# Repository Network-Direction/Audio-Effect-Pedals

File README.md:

# Effects Pedal Resources
Schematics and other resources for building effects pedals.

Schematics are drawn in Kicad.

Sometimes fabrication files are included, for use with services such as JLCPCB.

Enclosure templates show how to drill an enclosure.

</br></br>

# Pedals
Distortion:
* Big Muff Pi
* Boss BD2 Blues Driver (original and modified)
* OpAmp Distortion pedal
* Klon Centaur
* MXR Distortion
* ProCo RAT

</br></br>

Other:
* Boss CE-2 Chorus
* Boss PH-1r Phaser
* MXR Dyna Comp

</br></br>

# Audio Theory
Learn the basics of how sound works, at least as far as it relates to effects pedals.

See the Wiki page for more.

</br></br>

# Audio Circuit Blocks
Learn how some of the circuit blocks common in effects pedals work.

# KiCad Components
Additional libraries for KiCad, for components that don't exist by default.

</br></br>

# Stomp Breakout
A small breakout board for the stomp switch, and parts that connect to it.

</br></br>

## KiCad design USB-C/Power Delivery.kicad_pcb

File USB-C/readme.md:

# USB-C Power

A USB power system supplying 4x 9v outputs, up tp 2A or current.

Requires a USB-C charger capable of 9v/2A or better. A red LED turns on of there's an error negotiating power.

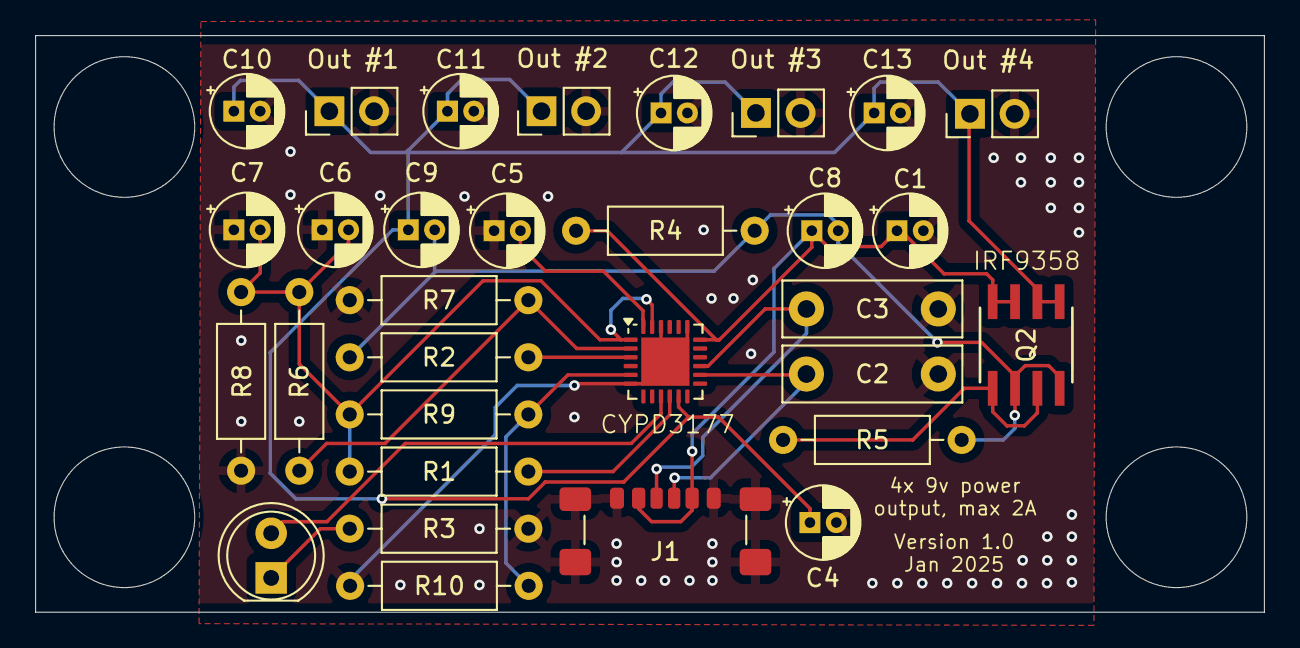
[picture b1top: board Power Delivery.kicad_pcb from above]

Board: 2 copper layers, 69.9 x 32.8 mm, 31 parts (0 on the bottom side), 15 nets.

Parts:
C1: 3.3uF; CP_Radial_D4.0mm_P1.50mm
C2, C3: 470pf; C_Rect_L10.0mm_W3.0mm_P7.50mm_MKS4
C4, C5, C6, C8, C9: 1uF; CP_Radial_D4.0mm_P1.50mm
C7: 0.1uF; CP_Radial_D4.0mm_P1.50mm
C10, C11, C12, C13: 100uF; CP_Radial_D4.0mm_P1.50mm
D1: LED; LED_D5.0mm
J1: USB4125-GF-A; USB_C_Receptacle_GCT_USB4135-GF-A_6P_TopMnt_Horizontal
J2: Out #3; PinHeader_1x02_P2.54mm_Vertical
J3: Out #1; PinHeader_1x02_P2.54mm_Vertical
J4: Out #2; PinHeader_1x02_P2.54mm_Vertical
J5: Out #4; PinHeader_1x02_P2.54mm_Vertical
Q2: IRF9358-TRPBF
R1: 4K7; R_Axial_DIN0207_L6.3mm_D2.5mm_P10.16mm_Horizontal
R2, R7: 1K; R_Axial_DIN0207_L6.3mm_D2.5mm_P10.16mm_Horizontal
R3, R10: 2K4; R_Axial_DIN0207_L6.3mm_D2.5mm_P10.16mm_Horizontal
R4: 10K; R_Axial_DIN0207_L6.3mm_D2.5mm_P10.16mm_Horizontal
R5: 47K; R_Axial_DIN0207_L6.3mm_D2.5mm_P10.16mm_Horizontal
R6, R8, R9: 5K1; R_Axial_DIN0207_L6.3mm_D2.5mm_P10.16mm_Horizontal
U1: CYPD3177-24LQ; QFN-24-1EP_4x4mm_P0.5mm_EP2.75x2.75mm

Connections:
3.3v: C6.2, C7.2, R1.2, R6.1, R8.1, R9.1, U1.1 (VBUS_MIN), U1.23 (VDDD)
GND: C1.2, C2.2, C3.2, C4.2, C5.1, C6.1, C7.1, C10.2, C11.2, C12.2, C13.2, J1.A12 (GND), J1.B12 (GND), J1.S1 (SHIELD), J2.2, J3.2, J4.2, J5.2, R3.1, R7.1, R8.2, R10.1, U1.6 (ISNK_FINE), U1.19 (GND), U1.22 (GND), U1.25 (GND)
unnamed: C8.2, C9.2, Q2.2, Q2.4, R2.1, R4.2, R5.2
unnamed: D1.2 (A), U1.9 (FAULT)
unnamed: D1.1 (K), R3.2
unnamed: C3.1, J1.A5 (CC1), U1.15 (CC1)
unnamed: C2.1, J1.B5 (CC2), U1.14 (CC2)
unnamed: C4.1, C9.1, C10.1, C11.1, C12.1, C13.1, J2.1, J3.1, J4.1, J5.1, Q2.5, Q2.6, U1.11 (VDC_OUT)
unnamed: Q2.1, Q2.3, R5.1
unnamed: R1.1, U1.10 (FLIP)
unnamed: R9.2, R10.2, U1.5 (ISNK_COARSE)
unnamed: R2.2, U1.3 (VBUS_FET_EN)
unnamed: C1.1, C8.1, J1.A9 (VBUS), J1.B9 (VBUS), Q2.7, Q2.8, R4.1, U1.18 (VBUS_IN)
unnamed: R6.2, R7.2, U1.2 (VBUS_MAX)
unnamed: C5.2, U1.24 (VCCD)

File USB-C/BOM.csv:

"Reference","Value","Datasheet","Footprint","Qty","DNP"
"C1","3.3uF","~","Capacitor_THT:CP_Radial_D4.0mm_P1.50mm","1",""
"C2,C3","470pf","~","Capacitor_THT:C_Rect_L10.0mm_W3.0mm_P7.50mm_MKS4","2",""
"C4,C5,C6,C8,C9","1uF","~","Capacitor_THT:CP_Radial_D4.0mm_P1.50mm","5",""
"C7","0.1uF","~","Capacitor_THT:CP_Radial_D4.0mm_P1.50mm","1",""
"C10,C11,C12,C13","100uF","~","Capacitor_THT:CP_Radial_D4.0mm_P1.50mm","4",""
"D1","LED","~","LED_THT:LED_D5.0mm","1",""
"J1","USB4125-GF-A","https://www.usb.org/sites/default/files/documents/usb_type-c.zip","Connector_USB:USB_C_Receptacle_GCT_USB4135-GF-A_6P_TopMnt_Horizontal","1",""
"J2","Out #3","~","Connector_PinHeader_2.54mm:PinHeader_1x02_P2.54mm_Vertical","1",""
"J3","Out #1","~","Connector_PinHeader_2.54mm:PinHeader_1x02_P2.54mm_Vertical","1",""
"J4","Out #2","~","Connector_PinHeader_2.54mm:PinHeader_1x02_P2.54mm_Vertical","1",""
"J5","Out #4","~","Connector_PinHeader_2.54mm:PinHeader_1x02_P2.54mm_Vertical","1",""
"Q2","IRF9358-TRPBF","IRF9358TRPBF","custom:IRF9358-TRPBF","1",""
"R1","4K7","~","Resistor_THT:R_Axial_DIN0207_L6.3mm_D2.5mm_P10.16mm_Horizontal","1",""
"R2,R7","1K","~","Resistor_THT:R_Axial_DIN0207_L6.3mm_D2.5mm_P10.16mm_Horizontal","2",""
"R3,R10","2K4","~","Resistor_THT:R_Axial_DIN0207_L6.3mm_D2.5mm_P10.16mm_Horizontal","2",""
"R4","10K","~","Resistor_THT:R_Axial_DIN0207_L6.3mm_D2.5mm_P10.16mm_Horizontal","1",""
"R5","47K","~","Resistor_THT:R_Axial_DIN0207_L6.3mm_D2.5mm_P10.16mm_Horizontal","1",""
"R6,R8,R9","5K1","~","Resistor_THT:R_Axial_DIN0207_L6.3mm_D2.5mm_P10.16mm_Horizontal","3",""
"U1","CYPD3177-24LQ","https://www.infineon.com/dgdl/Infineon-EZ-PD_BCR_Datasheet_U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","Package_DFN_QFN:QFN-24-1EP_4x4mm_P0.5mm_EP2.75x2.75mm","1",""

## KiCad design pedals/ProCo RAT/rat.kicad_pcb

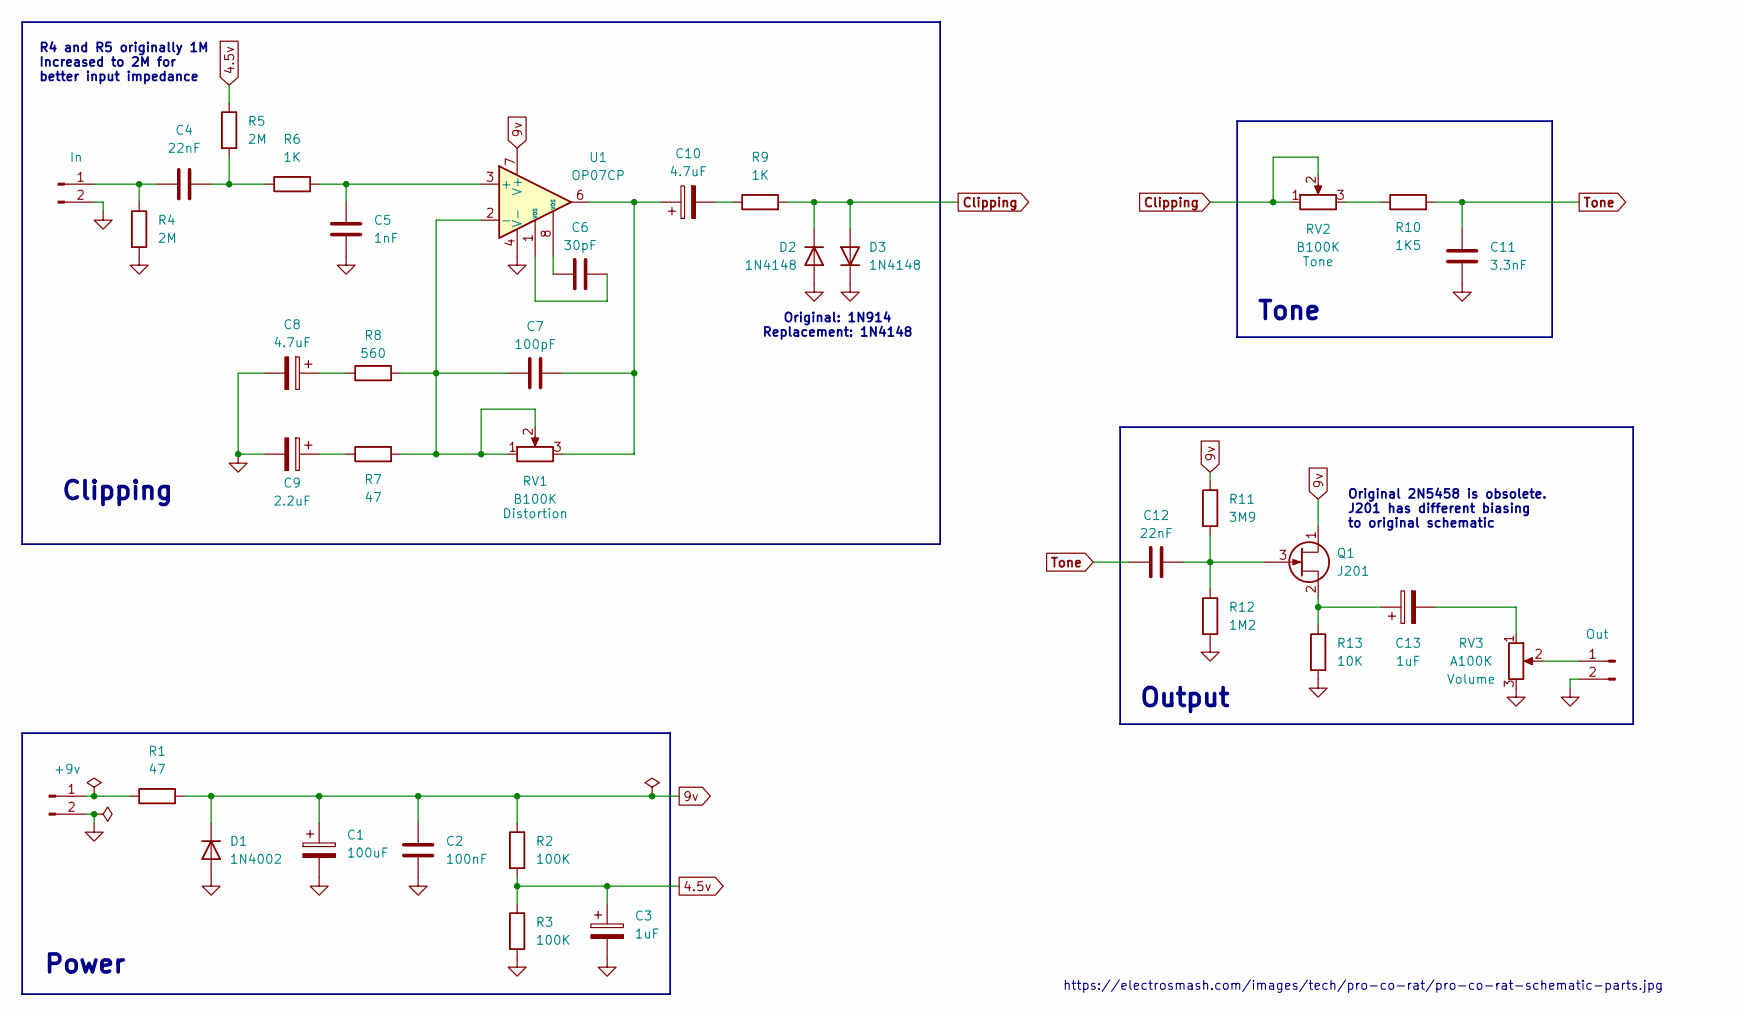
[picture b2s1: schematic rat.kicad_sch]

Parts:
C1: 100uF; CP_Radial_D6.3mm_P2.50mm
C2: 100nF; C_Rect_L7.2mm_W2.5mm_P5.00mm_FKS2_FKP2_MKS2_MKP2
C3, C13: 1uF; CP_Radial_D4.0mm_P1.50mm
C4, C12: 22nF; C_Rect_L7.2mm_W2.5mm_P5.00mm_FKS2_FKP2_MKS2_MKP2
C5: 1nF; C_Rect_L7.2mm_W2.5mm_P5.00mm_FKS2_FKP2_MKS2_MKP2
C6: 30pF; C_Disc_D3.8mm_W2.6mm_P2.50mm
C7: 100pF; C_Disc_D5.1mm_W3.2mm_P5.00mm
C8, C10: 4.7uF; CP_Radial_D4.0mm_P1.50mm
C9: 2.2uF; C_Rect_L7.2mm_W2.5mm_P5.00mm_FKS2_FKP2_MKS2_MKP2
C11: 3.3nF; C_Rect_L7.2mm_W2.5mm_P5.00mm_FKS2_FKP2_MKS2_MKP2
D1: 1N4002; D_DO-34_SOD68_P7.62mm_Horizontal
D2, D3: 1N4148; D_DO-34_SOD68_P7.62mm_Horizontal
J1: +9v; PinHeader_1x02_P2.54mm_Vertical
J2: In; PinHeader_1x02_P2.54mm_Vertical
J3: Out; PinHeader_1x02_P2.54mm_Vertical
Q1: J201; SOT-23_Handsoldering
R1, R7: 47; R_Axial_DIN0207_L6.3mm_D2.5mm_P10.16mm_Horizontal
R2, R3: 100K; R_Axial_DIN0207_L6.3mm_D2.5mm_P10.16mm_Horizontal
R4, R5: 2M; R_Axial_DIN0207_L6.3mm_D2.5mm_P10.16mm_Horizontal
R6, R9: 1K; R_Axial_DIN0207_L6.3mm_D2.5mm_P10.16mm_Horizontal
R8: 560; R_Axial_DIN0207_L6.3mm_D2.5mm_P10.16mm_Horizontal
R10: 1K5; R_Axial_DIN0207_L6.3mm_D2.5mm_P10.16mm_Horizontal
R11: 3M9; R_Axial_DIN0207_L6.3mm_D2.5mm_P10.16mm_Horizontal
R12: 1M2; R_Axial_DIN0207_L6.3mm_D2.5mm_P10.16mm_Horizontal
R13: 10K; R_Axial_DIN0207_L6.3mm_D2.5mm_P10.16mm_Horizontal
RV1, RV2: B100K; PinHeader_1x03_P2.54mm_Vertical
RV3: A100K; PinHeader_1x03_P2.54mm_Vertical
U1: OP07CP; DIP-8_W7.62mm

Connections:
4.5v: C3.1, R2.2, R3.1, R5.1
9v: C1.1, C2.1, D1.1 (K), Q1.1 (D), R1.2, R2.1, R11.1, U1.7 (V+)
Clipping: D2.1 (K), D3.2 (A), R9.2, RV2.1, RV2.2
GND: C1.2, C2.2, C3.2, C5.2, C8.2, C9.2, C11.2, D1.2 (A), D2.2 (A), D3.1 (K), J1.2, J2.2, J3.2, R3.2, R4.2, R12.2, R13.2, RV3.3, U1.4 (V-)
unnamed: C4.2, R5.2, R6.1
unnamed: C6.1, U1.1 (VOS)
unnamed: C6.2, U1.8 (VOS)
unnamed: C8.1, R8.1
unnamed: C9.1, R7.1
unnamed: C7.1, C10.1, RV1.3, U1.6
unnamed: C10.2, R9.1
unnamed: C13.2, RV3.1
unnamed: J1.1, R1.1
unnamed: C4.1, J2.1, R4.1
unnamed: J3.1, RV3.2
unnamed: C12.1, Q1.3 (G), R11.2, R12.1
unnamed: C13.1, Q1.2 (S), R13.1
unnamed: R10.1, RV2.3
unnamed: C5.1, R6.2, U1.3 (+)
unnamed: C7.2, R7.2, R8.2, RV1.1, RV1.2, U1.2 (-)
Tone: C11.1, C12.2, R10.2

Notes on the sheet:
Output
Power
https://electrosmash.com/images/tech/pro-co-rat/pro-co-rat-schematic-parts.jpg
Clipping
Tone
R4 and R5 originally 1M Increased to 2M for better input impedance
Original: 1N914 Replacement: 1N4148
Original 2N5458 is obsolete. J201 has different biasing to original schematic

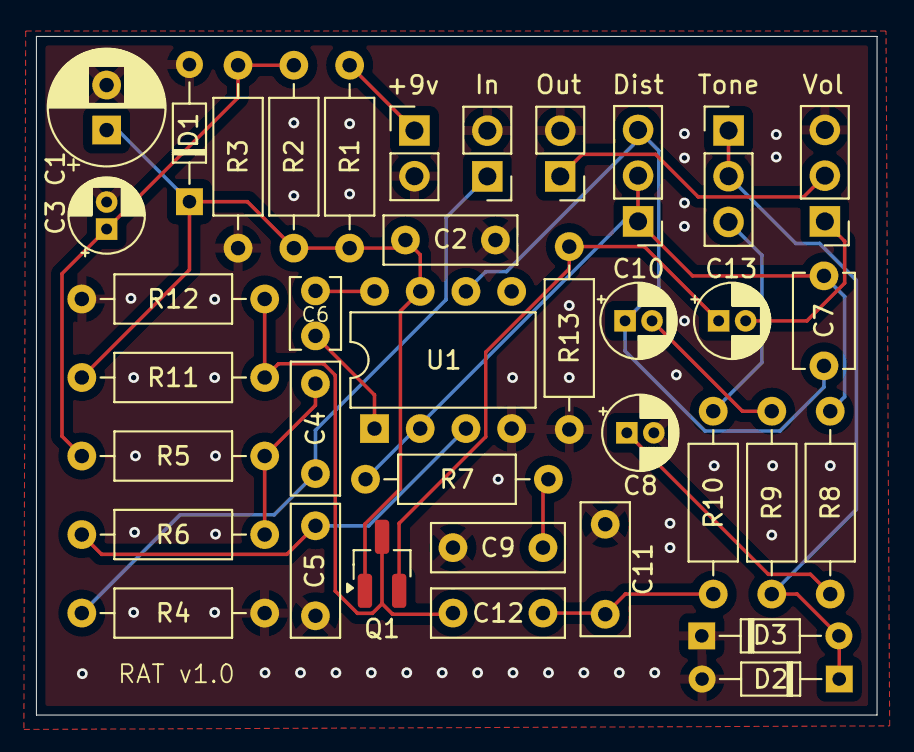
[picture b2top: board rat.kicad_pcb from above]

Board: 2 copper layers, 46.7 x 37.7 mm, 37 parts (0 on the bottom side), 21 nets.

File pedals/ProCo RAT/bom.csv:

"Id";"Designator";"Footprint";"Quantity";"Designation";"Supplier and ref";
1;"RV2,RV1";"PinHeader_1x03_P2.54mm_Vertical";2;"B100K";;;
2;"C8,C10";"CP_Radial_D4.0mm_P1.50mm";2;"4.7uF";;;
3;"Q1";"SOT-23_Handsoldering";1;"J201";;;
4;"U1";"DIP-8_W7.62mm";1;"OP07CP";;;
5;"C3,C13";"CP_Radial_D4.0mm_P1.50mm";2;"1uF";;;
6;"R12";"R_Axial_DIN0207_L6.3mm_D2.5mm_P10.16mm_Horizontal";1;"1M2";;;
7;"R6,R9";"R_Axial_DIN0207_L6.3mm_D2.5mm_P10.16mm_Horizontal";2;"1K";;;
8;"J1";"PinHeader_1x02_P2.54mm_Vertical";1;"+9v";;;
9;"D1";"D_DO-34_SOD68_P7.62mm_Horizontal";1;"1N4002";;;
10;"C12,C4";"C_Rect_L7.2mm_W2.5mm_P5.00mm_FKS2_FKP2_MKS2_MKP2";2;"22nF";;;
11;"C9";"C_Rect_L7.2mm_W2.5mm_P5.00mm_FKS2_FKP2_MKS2_MKP2";1;"2.2uF";;;
12;"J2";"PinHeader_1x02_P2.54mm_Vertical";1;"In";;;
13;"C7";"C_Disc_D5.1mm_W3.2mm_P5.00mm";1;"100pF";;;
14;"C2";"C_Rect_L7.2mm_W2.5mm_P5.00mm_FKS2_FKP2_MKS2_MKP2";1;"100nF";;;
15;"R13";"R_Axial_DIN0207_L6.3mm_D2.5mm_P10.16mm_Horizontal";1;"10K";;;
16;"R4,R5";"R_Axial_DIN0207_L6.3mm_D2.5mm_P10.16mm_Horizontal";2;"2M";;;
17;"R2,R3";"R_Axial_DIN0207_L6.3mm_D2.5mm_P10.16mm_Horizontal";2;"100K";;;
18;"C1";"CP_Radial_D6.3mm_P2.50mm";1;"100uF";;;
19;"R8";"R_Axial_DIN0207_L6.3mm_D2.5mm_P10.16mm_Horizontal";1;"560";;;
20;"C5";"C_Rect_L7.2mm_W2.5mm_P5.00mm_FKS2_FKP2_MKS2_MKP2";1;"1nF";;;
21;"RV3";"PinHeader_1x03_P2.54mm_Vertical";1;"A100K";;;
22;"C6";"C_Disc_D3.8mm_W2.6mm_P2.50mm";1;"30pF";;;
23;"D3,D2";"D_DO-34_SOD68_P7.62mm_Horizontal";2;"1N4148";;;
24;"J3";"PinHeader_1x02_P2.54mm_Vertical";1;"Out";;;
25;"R7,R1";"R_Axial_DIN0207_L6.3mm_D2.5mm_P10.16mm_Horizontal";2;"47";;;
26;"R10";"R_Axial_DIN0207_L6.3mm_D2.5mm_P10.16mm_Horizontal";1;"1K5";;;
27;"R11";"R_Axial_DIN0207_L6.3mm_D2.5mm_P10.16mm_Horizontal";1;"3M9";;;
28;"C11";"C_Rect_L7.2mm_W2.5mm_P5.00mm_FKS2_FKP2_MKS2_MKP2";1;"3.3nF";;;

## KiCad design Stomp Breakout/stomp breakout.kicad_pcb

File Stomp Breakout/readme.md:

# Stomp Breakout PCB

A PCB that allows a stomp switch to be soldered, automatically handling wiring.

Input and output jacks, as well as power are connected to the breakout.

Includes an option for a resistor and LED to show when the pedal is in bypass mode.

## Status

Schematic and PCB designed, but not yet tested.

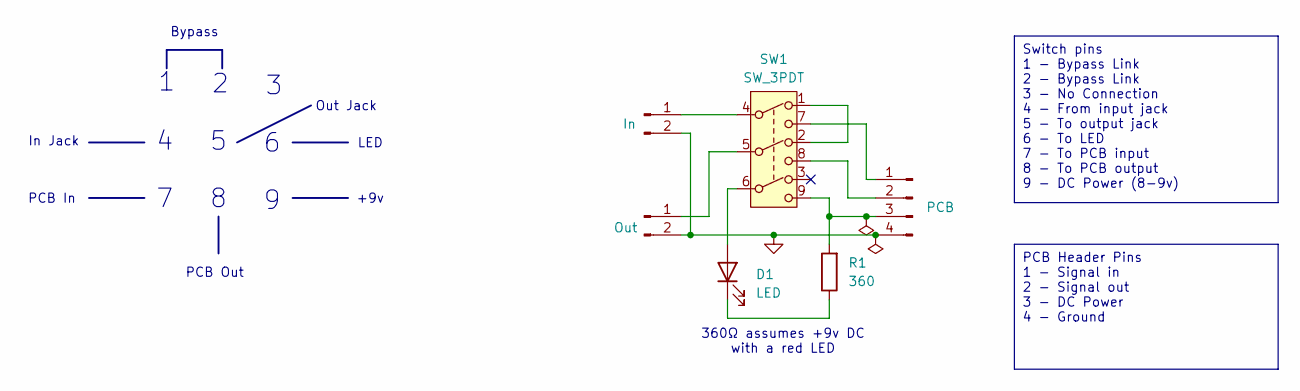
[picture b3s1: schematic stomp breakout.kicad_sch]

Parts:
D1: LED; LED_D5.0mm
J1: In; PinHeader_1x02_P2.54mm_Horizontal
J2: Out; PinHeader_1x02_P2.54mm_Horizontal
J3: PCB; PinHeader_1x04_P2.54mm_Horizontal
R1: 360; R_Axial_DIN0207_L6.3mm_D2.5mm_P7.62mm_Horizontal
SW1: SW_3PDT; 3PDT Stomp Switch

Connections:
GND: J1.2, J2.2, J3.4
unnamed: D1.2 (A), SW1.6
unnamed: D1.1 (K), R1.1
unnamed: J1.1, SW1.4
unnamed: J2.1, SW1.5
unnamed: J3.1, SW1.7
unnamed: J3.2, SW1.8
unnamed: J3.3, R1.2, SW1.9
unnamed: SW1.1, SW1.2

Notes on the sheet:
PCB Header Pins 1 - Signal in 2 - Signal out 3 - DC Power 4 - Ground
Switch pins 1 - Bypass Link 2 - Bypass Link 3 - No Connection 4 - From input jack 5 - To output jack 6 - To LED 7 - To PCB input 8 - To PCB output 9 - DC Power (8-9v)
Out Jack
In Jack
Bypass
PCB Out
360Ω assumes +9v DC with a red LED
LED
PCB In
+9v

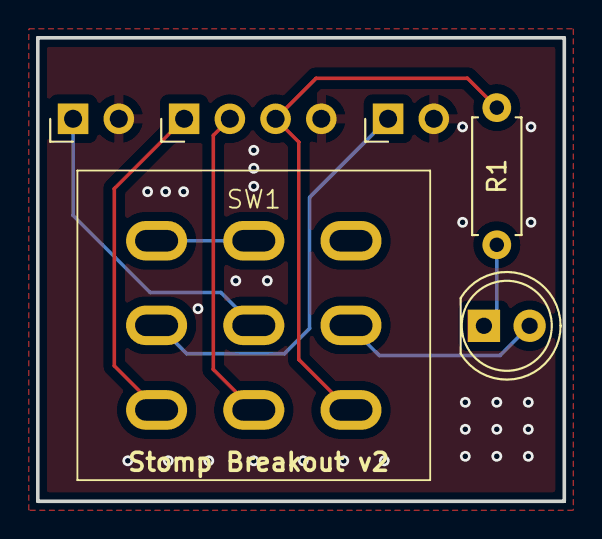
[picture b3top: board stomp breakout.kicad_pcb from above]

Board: 2 copper layers, 29.2 x 25.8 mm, 6 parts (0 on the bottom side), 9 nets.

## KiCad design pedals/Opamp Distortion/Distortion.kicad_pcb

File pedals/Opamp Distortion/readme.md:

# OpAmp Distortion

# Status
Tested on the PCB
PCB printed but not yet tested.

# Notes
A custom distortion pedal based on OpAmp rail clipping

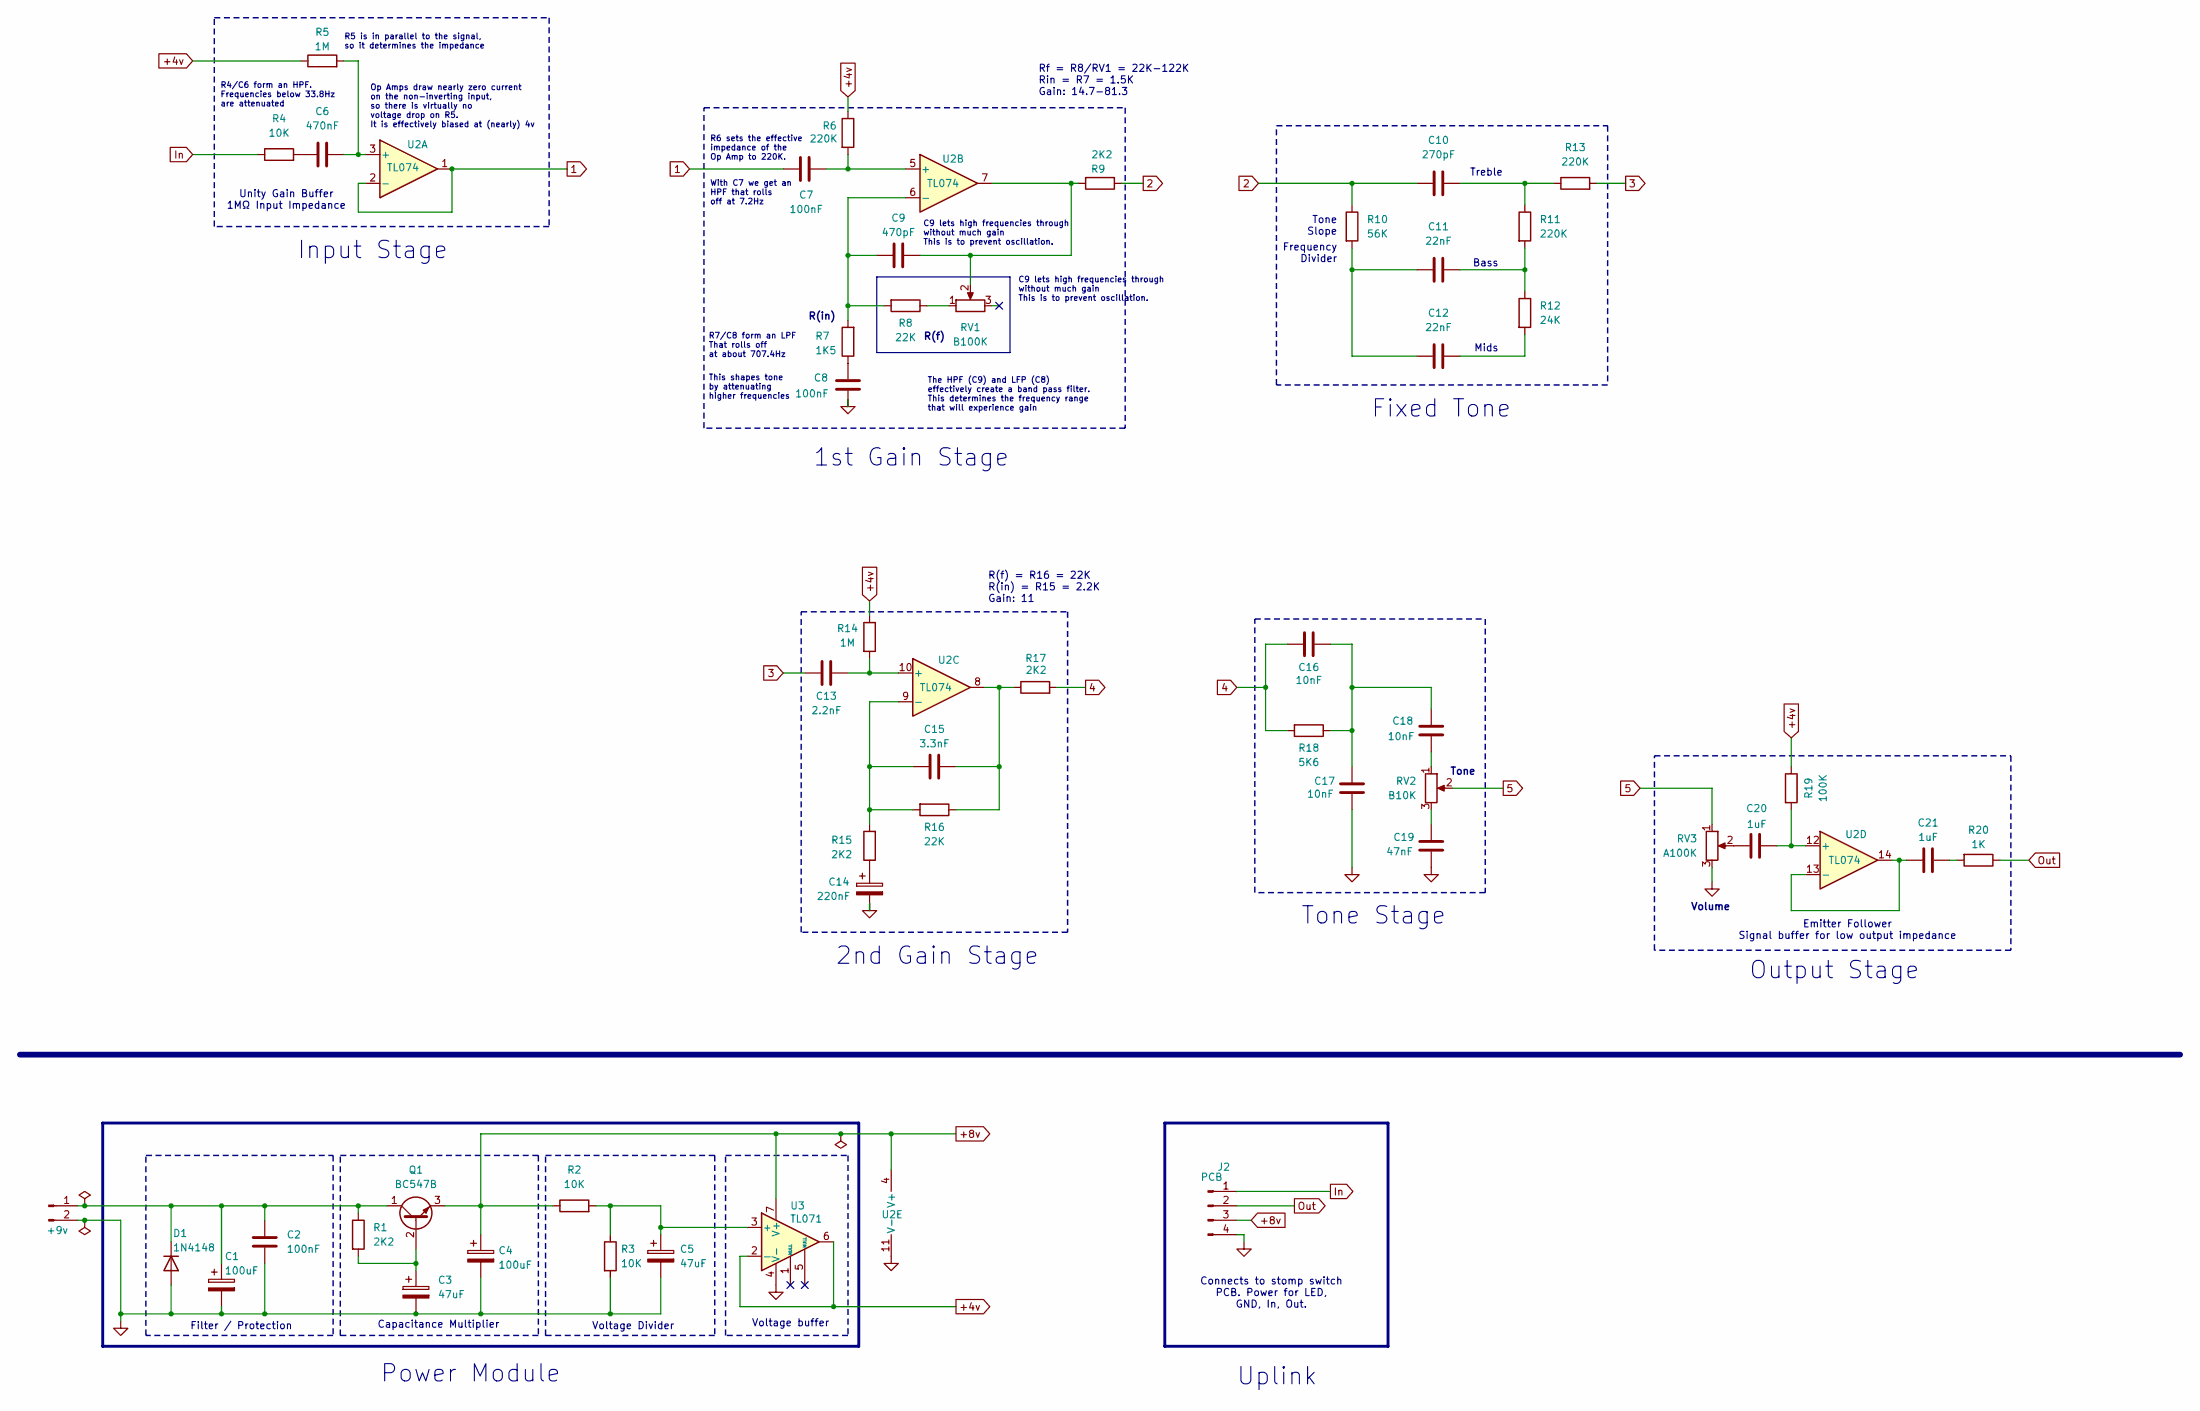
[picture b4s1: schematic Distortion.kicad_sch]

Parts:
C1, C4: 100uF; CP_Radial_D6.3mm_P2.50mm
C2, C7, C8: 100nF; C_Rect_L7.2mm_W2.5mm_P5.00mm_FKS2_FKP2_MKS2_MKP2
C3, C5: 47uF; CP_Radial_D5.0mm_P2.00mm
C6: 470nF; C_Rect_L7.2mm_W3.5mm_P5.00mm_FKS2_FKP2_MKS2_MKP2
C9: 470pF; C_Disc_D3.8mm_W2.6mm_P2.50mm
C10: 270pF; C_Disc_D5.0mm_W2.5mm_P2.50mm
C11, C12: 22nF; C_Rect_L7.2mm_W2.5mm_P5.00mm_FKS2_FKP2_MKS2_MKP2
C13: 2.2nF; C_Rect_L7.2mm_W2.5mm_P5.00mm_FKS2_FKP2_MKS2_MKP2
C14: 220nF; C_Rect_L7.2mm_W2.5mm_P5.00mm_FKS2_FKP2_MKS2_MKP2
C15: 3.3nF; C_Rect_L7.2mm_W2.5mm_P5.00mm_FKS2_FKP2_MKS2_MKP2
C16, C17, C18: 10nF; C_Rect_L7.2mm_W2.5mm_P5.00mm_FKS2_FKP2_MKS2_MKP2
C19: 47nF; C_Rect_L7.2mm_W2.5mm_P5.00mm_FKS2_FKP2_MKS2_MKP2
C20, C21: 1uF; C_Rect_L9.0mm_W5.1mm_P7.50mm_MKT
D1: 1N4148; D_DO-34_SOD68_P7.62mm_Horizontal
J1: +9v; PinHeader_1x02_P2.54mm_Horizontal
J2: PCB; PinHeader_1x04_P2.54mm_Horizontal
Q1: BC547B; TO-92_Inline_Wide
R1, R9, R15, R17: 2K2; R_Axial_DIN0207_L6.3mm_D2.5mm_P10.16mm_Horizontal
R2, R3, R4: 10K; R_Axial_DIN0207_L6.3mm_D2.5mm_P10.16mm_Horizontal
R5, R14: 1M; R_Axial_DIN0207_L6.3mm_D2.5mm_P10.16mm_Horizontal
R6, R11, R13: 220K; R_Axial_DIN0207_L6.3mm_D2.5mm_P10.16mm_Horizontal
R7: 1K5; R_Axial_DIN0207_L6.3mm_D2.5mm_P10.16mm_Horizontal
R8, R16: 22K; R_Axial_DIN0207_L6.3mm_D2.5mm_P10.16mm_Horizontal
R10: 56K; R_Axial_DIN0207_L6.3mm_D2.5mm_P10.16mm_Horizontal
R12: 24K; R_Axial_DIN0207_L6.3mm_D2.5mm_P10.16mm_Horizontal
R18: 5K6; R_Axial_DIN0207_L6.3mm_D2.5mm_P10.16mm_Horizontal
R19: 100K; R_Axial_DIN0207_L6.3mm_D2.5mm_P10.16mm_Horizontal
R20: 1K; R_Axial_DIN0207_L6.3mm_D2.5mm_P10.16mm_Horizontal
RV1: B100K; PinHeader_1x03_P2.54mm_Horizontal
RV2: B10K; PinHeader_1x03_P2.54mm_Horizontal
RV3: A100K; PinHeader_1x03_P2.54mm_Horizontal
U2: TL074; DIP-14_W7.62mm
U3: TL071; DIP-8_W7.62mm

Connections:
1: C7.1, U2.1, U2.2 (-)
2: C10.1, R9.1, R10.1
3: C13.1, R13.2
4: C16.1, R17.2, R18.2
5: RV2.2, RV3.1
+4v: R5.1, R6.1, R14.1, R19.1, U3.2 (-), U3.6
+8v: C4.1, J2.3, Q1.3 (E), R2.1, U2.4 (V+), U3.7 (V+)
GND: C1.2, C2.2, C3.2, C4.2, C5.2, C8.1, C14.2, C17.1, C19.1, D1.2 (A), J1.2, J2.4, R3.2, RV3.3, U2.11 (V-), U3.4 (V-)
In: J2.1, R4.1
unnamed: C6.1, R4.2
unnamed: C8.2, R7.1
unnamed: C9.2, R9.2, RV1.2, U2.7
unnamed: C10.2, R11.1, R13.1
unnamed: C11.1, C12.1, R10.2
unnamed: C11.2, R11.2, R12.1
unnamed: C12.2, R12.2
unnamed: C14.1, R15.1
unnamed: C15.2, R16.1, R17.1, U2.8
unnamed: C16.2, C17.2, C18.2, R18.1
unnamed: C18.1, RV2.1
unnamed: C19.2, RV2.3
unnamed: C20.1, RV3.2
unnamed: C21.2, R20.2
unnamed: C1.1, C2.1, D1.1 (K), J1.1, Q1.1 (C), R1.1
unnamed: C3.1, Q1.2 (B), R1.2
unnamed: R8.1, RV1.1
unnamed: C6.2, R5.2, U2.3 (+)
unnamed: C7.2, R6.2, U2.5 (+)
unnamed: C9.1, R7.2, R8.2, U2.6 (-)
unnamed: C13.2, R14.2, U2.10 (+)
unnamed: C15.1, R15.2, R16.2, U2.9 (-)
unnamed: C20.2, R19.2, U2.12 (+)
unnamed: C21.1, U2.13 (-), U2.14
unnamed: C5.1, R2.2, R3.1, U3.3 (+)
Out: J2.2, R20.1

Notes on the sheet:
R5 is in parallel to the signal, so it determines the impedance
Capacitance Multiplier
Uplink
Volume
R6 sets the effective impedance of the Op Amp to 220K.
Output Stage
Connects to stomp switch PCB. Power for LED, GND, In, Out.
2nd Gain Stage
The HPF (C9) and LFP (C8) effectively create a band pass filter. This determines the frequency range that will experience gain
This shapes tone by attenuating higher frequencies
Tone
Voltage Divider
Treble
Bass
With C7 we get an HPF that rolls off at 7.2Hz
Frequency Divider
Mids
Input Stage
Filter / Protection
Tone Stage
R(f)
Voltage buffer
R4/C6 form an HPF. Frequencies below 33.8Hz are attenuated
Rf = R8/RV1 = 22K-122K Rin = R7 = 1.5K Gain: 14.7-81.3
R(in)
R7/C8 form an LPF That rolls off at about 707.4Hz
Op Amps draw nearly zero current on the non-inverting input, so there is virtually no voltage drop on R5. It is effectively biased at (nearly) 4v
Tone Slope
Power Module
1st Gain Stage
Fixed Tone
Emitter Follower Signal buffer for low output impedance
Unity Gain Buffer 1MΩ Input Impedance
C9 lets high frequencies through without much gain This is to prevent oscillation.
R(f) = R16 = 22K R(in) = R15 = 2.2K Gain: 11

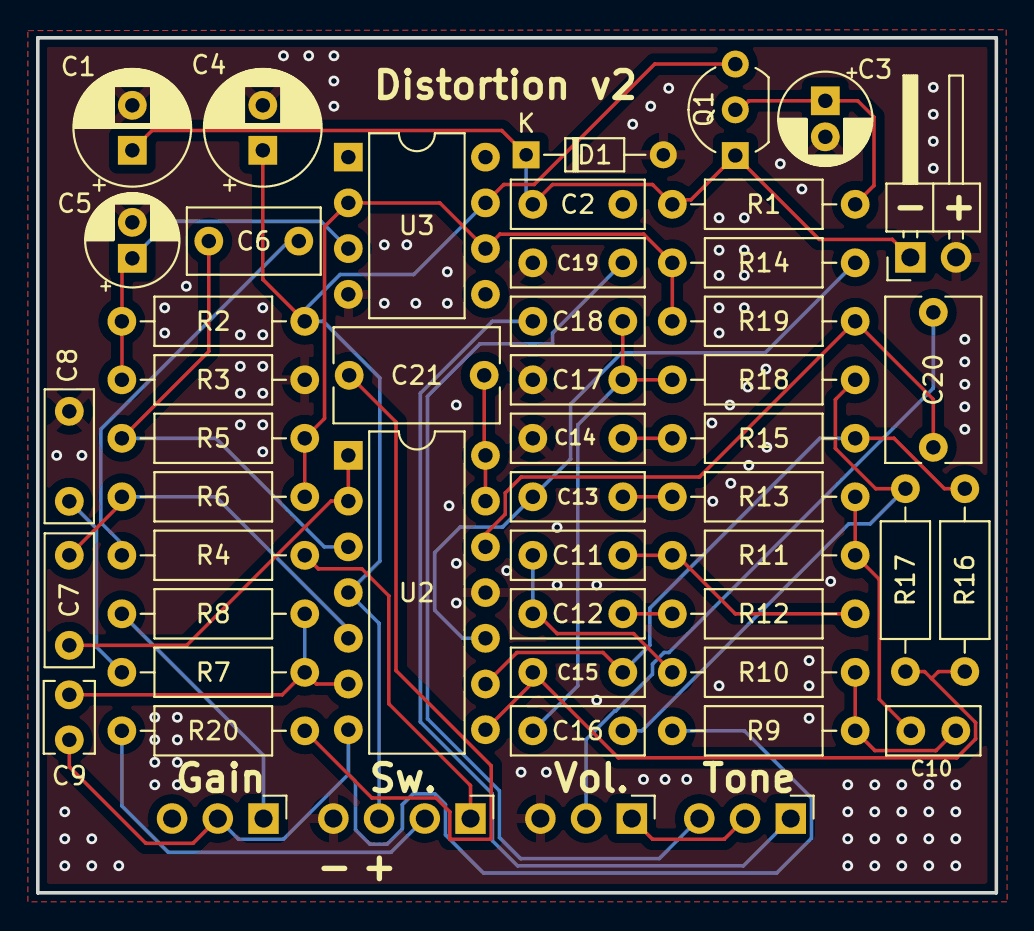
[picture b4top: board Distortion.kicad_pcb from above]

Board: 2 copper layers, 53.2 x 47.5 mm, 50 parts (0 on the bottom side), 35 nets.

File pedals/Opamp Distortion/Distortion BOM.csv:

Reference,Value,Qty
"C1,C4",100uF,2
"C2,C7,C8",100nF,3
"C3,C5",47uF,2
C6,470nF,1
C9,470pF,1
C10,270pF,1
"C11,C12",22nF,2
C13,2.2nF,1
C14,220nF,1
C15,3.3nF,1
"C16,C17,C18",10nF,3
C19,47nF,1
"C20,C21",1uF,2
D1,1N4148,1
J1,+9v,1
J2,In,1
J4,Out,1
Q1,BC547B,1
"R1,R9,R15,R17",2K2,4
"R2,R3,R4",10K,3
"R5,R14",1M,2
"R6,R11,R13",220K,3
R7,1K5,1
"R8,R16",22K,2
R10,56K,1
R12,24K,1
R18,5K6,1
R19,100K,1
R20,1K,1
RV1,B100K,1
RV2,B10K,1
RV3,A100K,1
U2,TL074,1
U3,TL071,1

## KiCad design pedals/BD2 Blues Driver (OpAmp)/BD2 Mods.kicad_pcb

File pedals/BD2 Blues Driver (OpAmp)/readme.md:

# Modified Blues Driver

# Status
Tested on the breadboard
PCB printed, not tested yet

# Notes
Modified to use TL072 JFET Opamp, rather than the original JFET transistors.

The gyrator section uses 56nF capacitors in the original circuit. This version adds the option to replace with the 47nF or 68nF caps. However, this might slightly reduce or increase the filtering.

# Links
_See the original BD2 files_

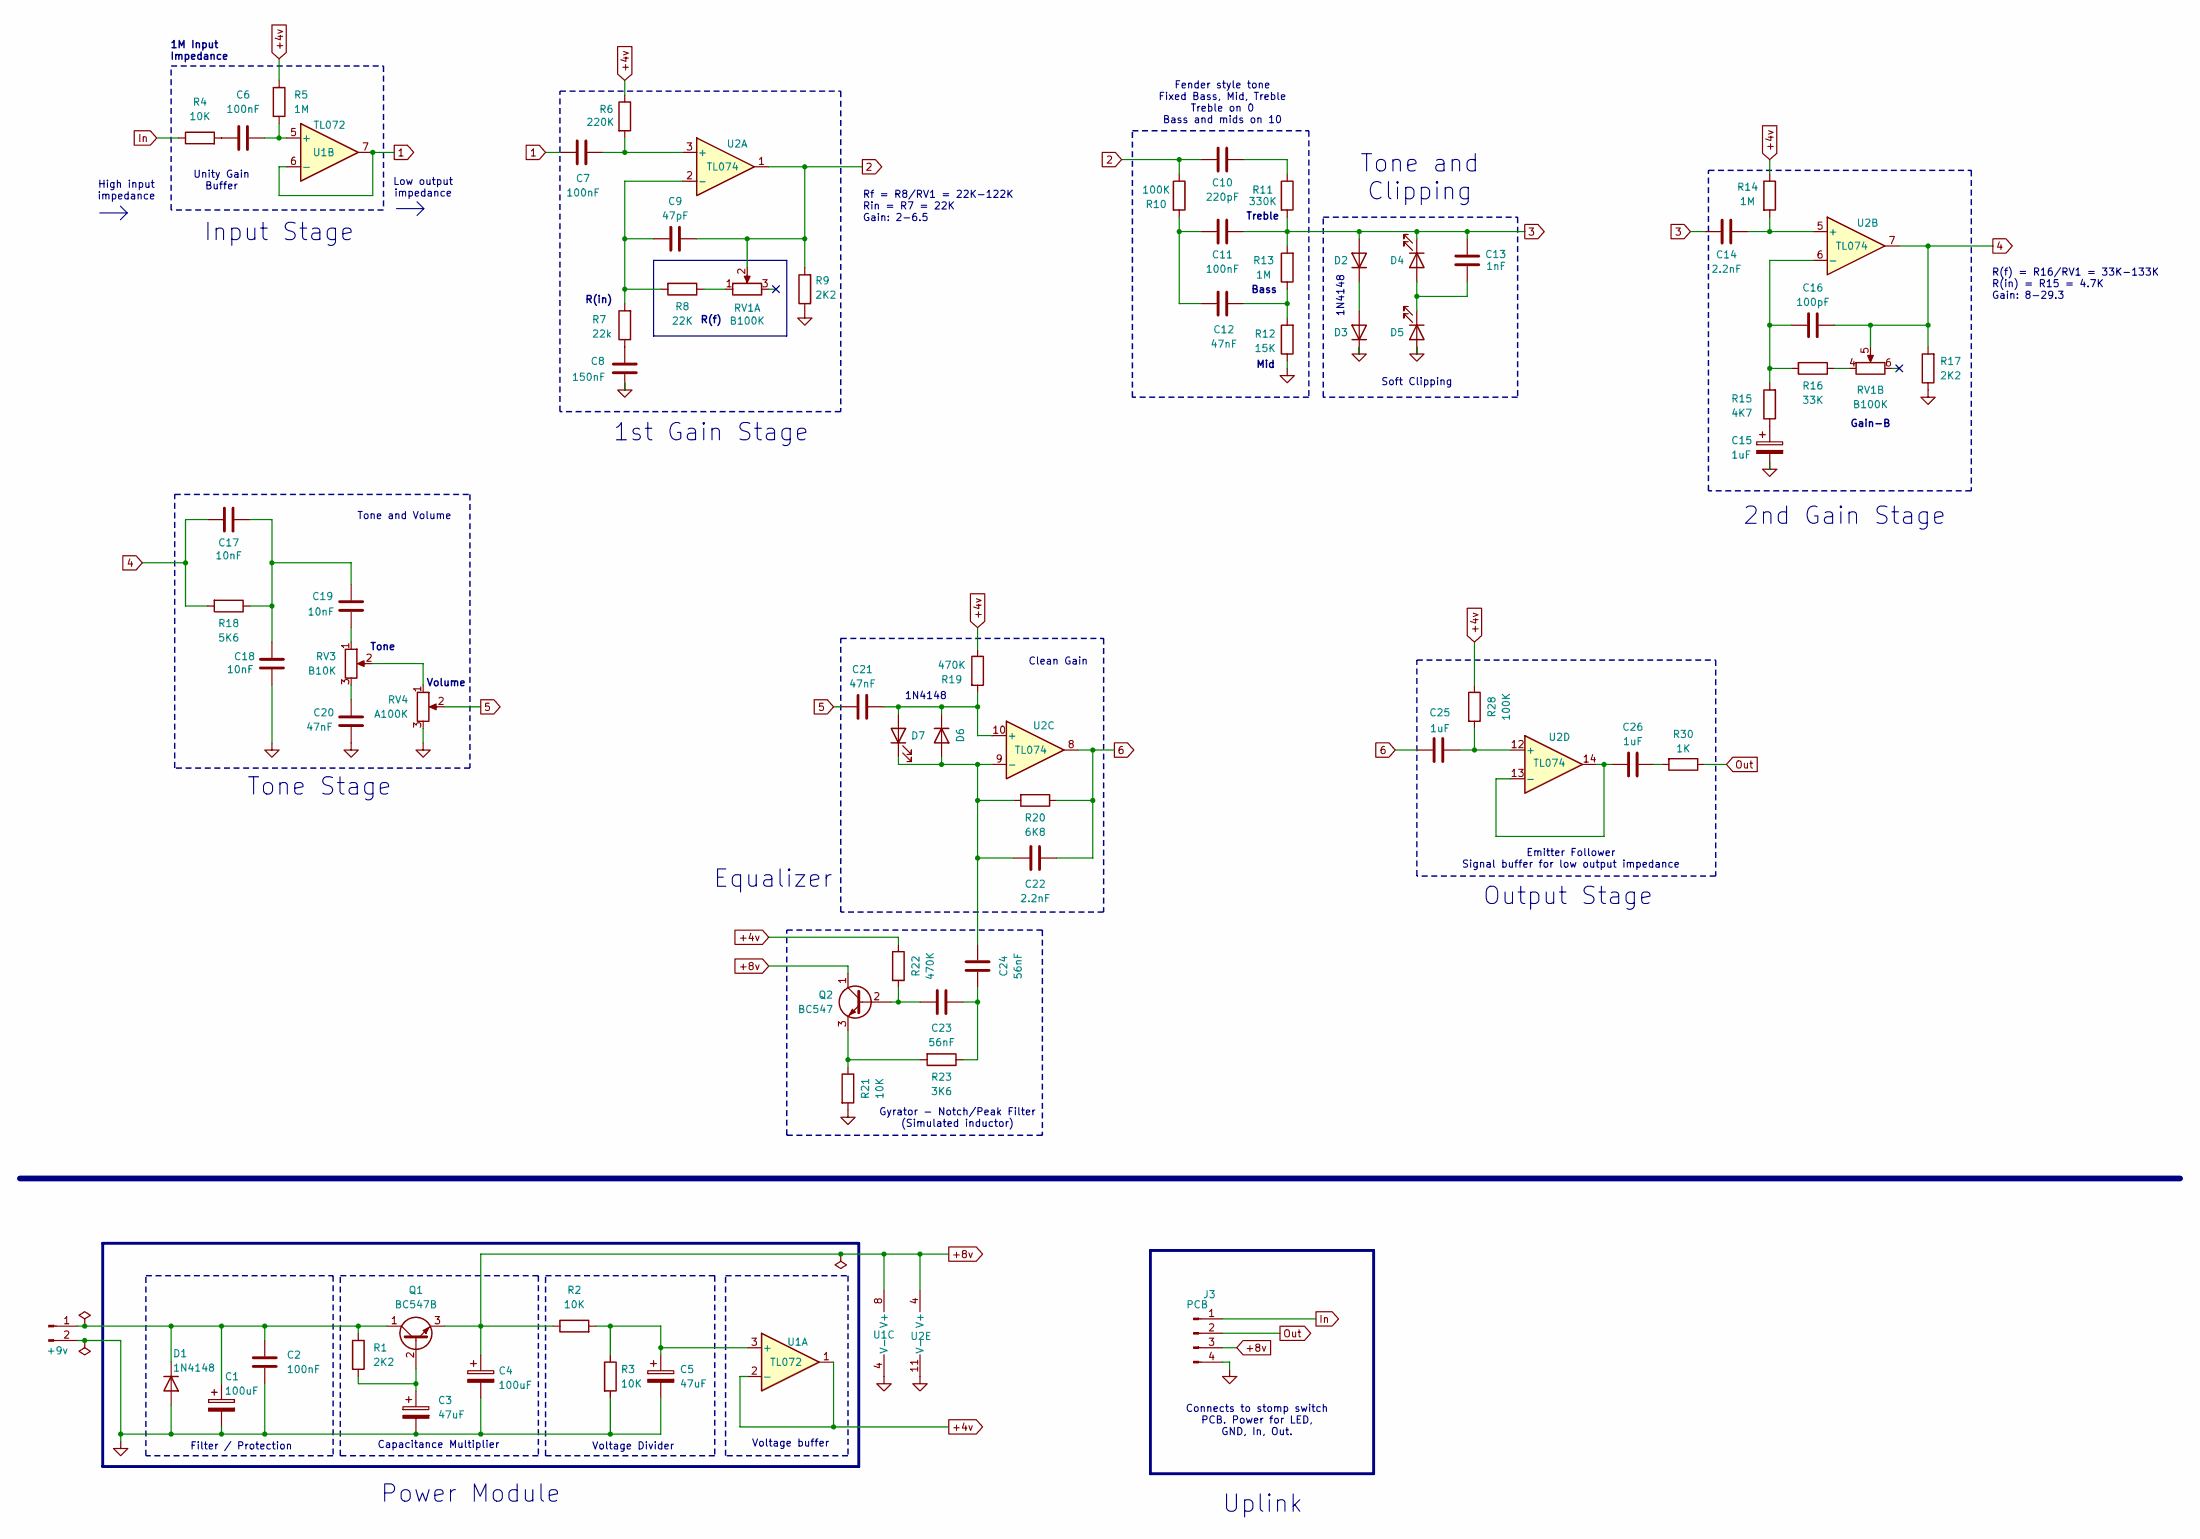
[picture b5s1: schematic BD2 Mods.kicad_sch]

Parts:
C1, C4: 100uF; CP_Radial_D6.3mm_P2.50mm
C2, C6, C7, C11: 100nF; C_Rect_L7.2mm_W2.5mm_P5.00mm_FKS2_FKP2_MKS2_MKP2
C3, C5: 47uF; CP_Radial_D5.0mm_P2.00mm
C8: 150nF; C_Rect_L7.2mm_W2.5mm_P5.00mm_FKS2_FKP2_MKS2_MKP2
C9: 47pF; C_Disc_D5.1mm_W3.2mm_P5.00mm
C10: 220pF; C_Disc_D5.1mm_W3.2mm_P5.00mm
C12, C20, C21: 47nF; C_Rect_L7.2mm_W2.5mm_P5.00mm_FKS2_FKP2_MKS2_MKP2
C13: 1nF; C_Rect_L7.2mm_W2.5mm_P5.00mm_FKS2_FKP2_MKS2_MKP2
C14, C22: 2.2nF; C_Rect_L7.2mm_W2.5mm_P5.00mm_FKS2_FKP2_MKS2_MKP2
C15: 1uF; CP_Radial_D4.0mm_P1.50mm
C16: 100pF; C_Disc_D5.1mm_W3.2mm_P5.00mm
C17, C18, C19: 10nF; C_Rect_L7.2mm_W2.5mm_P5.00mm_FKS2_FKP2_MKS2_MKP2
C23, C24: 56nF; C_Rect_L7.5mm_W6.5mm_P5.00mm
C25, C26: 1uF; C_Rect_L7.0mm_W6.0mm_P5.00mm
D1, D2, D3, D6: 1N4148; D_DO-35_SOD27_P7.62mm_Horizontal
D4, D5, D7: LED; LED_D5.0mm
J1: +9v; PinHeader_1x02_P2.54mm_Vertical
J3: PCB; PinHeader_1x04_P2.54mm_Vertical
Q1: BC547B; TO-92_Inline_Wide
Q2: BC547; TO-92_Inline_Wide
R1, R9, R17: 2K2; R_Axial_DIN0207_L6.3mm_D2.5mm_P10.16mm_Horizontal
R2, R3, R4, R21: 10K; R_Axial_DIN0207_L6.3mm_D2.5mm_P10.16mm_Horizontal
R5, R13, R14: 1M; R_Axial_DIN0207_L6.3mm_D2.5mm_P10.16mm_Horizontal
R6: 220K; R_Axial_DIN0207_L6.3mm_D2.5mm_P10.16mm_Horizontal
R7: 22k; R_Axial_DIN0207_L6.3mm_D2.5mm_P10.16mm_Horizontal
R8: 22K; R_Axial_DIN0207_L6.3mm_D2.5mm_P10.16mm_Horizontal
R10, R28: 100K; R_Axial_DIN0207_L6.3mm_D2.5mm_P10.16mm_Horizontal
R11: 330K; R_Axial_DIN0207_L6.3mm_D2.5mm_P10.16mm_Horizontal
R12: 15K; R_Axial_DIN0207_L6.3mm_D2.5mm_P10.16mm_Horizontal
R15: 4K7; R_Axial_DIN0207_L6.3mm_D2.5mm_P10.16mm_Horizontal
R16: 33K; R_Axial_DIN0207_L6.3mm_D2.5mm_P10.16mm_Horizontal
R18: 5K6; R_Axial_DIN0207_L6.3mm_D2.5mm_P10.16mm_Horizontal
R19, R22: 470K; R_Axial_DIN0207_L6.3mm_D2.5mm_P10.16mm_Horizontal
R20: 6K8; R_Axial_DIN0207_L6.3mm_D2.5mm_P10.16mm_Horizontal
R23: 3K6; R_Axial_DIN0207_L6.3mm_D2.5mm_P10.16mm_Horizontal
R30: 1K; R_Axial_DIN0207_L6.3mm_D2.5mm_P10.16mm_Horizontal
RV1: B100K; PinHeader_1x06_P2.54mm_Vertical
RV3: B10K; PinHeader_1x03_P2.54mm_Vertical
RV4: A100K; PinHeader_1x03_P2.54mm_Vertical
U1: TL072; DIP-8_W7.62mm
U2: TL074; DIP-14_W7.62mm

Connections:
1: C7.1, U1.6 (-), U1.7
2: C9.2, C10.1, R9.2, R10.1, RV1.2, U2.1
3: C11.2, C13.2, C14.1, D2.2 (A), D4.1 (K), R11.2, R13.2
4: C16.2, C17.1, R17.2, R18.2, RV1.5, U2.7
5: C21.1, RV4.2
6: C22.2, C25.1, R20.1, U2.8
+4v: R5.1, R6.1, R14.1, R19.1, R22.1, R28.1, U1.1, U1.2 (-)
+8v: C4.1, J3.3, Q1.3 (E), Q2.1 (C), R2.1, U1.8 (V+), U2.4 (V+)
GND: C1.2, C2.2, C3.2, C4.2, C5.2, C8.1, C15.2, C18.1, C20.1, D1.2 (A), D3.1 (K), D5.2 (A), J1.2, J3.4, R3.2, R9.1, R12.1, R17.1, R21.2, RV4.3, U1.4 (V-), U2.11 (V-)
In: J3.1, R4.1
unnamed: C6.1, R4.2
unnamed: C8.2, R7.1
unnamed: C10.2, R11.1
unnamed: C11.1, C12.2, R10.2
unnamed: C12.1, R12.2, R13.1
unnamed: C15.1, R15.1
unnamed: C17.2, C18.2, C19.2, R18.1
unnamed: C19.1, RV3.1
unnamed: C20.2, RV3.3
unnamed: C23.2, C24.1, R23.1
unnamed: C26.2, R30.2
unnamed: C1.1, C2.1, D1.1 (K), J1.1, Q1.1 (C), R1.1
unnamed: D2.1 (K), D3.2 (A)
unnamed: C13.1, D4.2 (A), D5.1 (K)
unnamed: C22.1, C24.2, D6.2 (A), D7.1 (K), R20.2, U2.9 (-)
unnamed: C21.2, D6.1 (K), D7.2 (A), R19.2, U2.10 (+)
unnamed: C3.1, Q1.2 (B), R1.2
unnamed: C23.1, Q2.2 (B), R22.2
unnamed: Q2.3 (E), R21.1, R23.2
unnamed: R8.1, RV1.1
unnamed: R16.1, RV1.4
unnamed: RV3.2, RV4.1
unnamed: C5.1, R2.2, R3.1, U1.3 (+)
unnamed: C6.2, R5.2, U1.5 (+)
unnamed: C7.2, R6.2, U2.3 (+)
unnamed: C9.1, R7.2, R8.2, U2.2 (-)
unnamed: C14.2, R14.2, U2.5 (+)
unnamed: C16.1, R15.2, R16.2, U2.6 (-)
unnamed: C25.2, R28.2, U2.12 (+)
unnamed: C26.1, U2.13 (-), U2.14
Out: J3.2, R30.1

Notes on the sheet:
1N4148
Capacitance Multiplier
Volume
Output Stage
2nd Gain Stage
Equalizer
Tone
Voltage Divider
Uplink
1M Input Impedance
Mid
Input Stage
Filter / Protection
Tone Stage
R(f)
Voltage buffer
Tone and Volume
Rf = R8/RV1 = 22K-122K Rin = R7 = 22K Gain: 2-6.5
Fender style tone Fixed Bass, Mid, Treble Treble on 0 Bass and mids on 10
R(in)
High input impedance
Treble
Low output impedance
Connects to stomp switch PCB. Power for LED, GND, In, Out.
Clean Gain
Soft Clipping
Power Module
Bass
Gain-B
1st Gain Stage
Tone and Clipping
Emitter Follower Signal buffer for low output impedance
Unity Gain Buffer
R(f) = R16/RV1 = 33K-133K R(in) = R15 = 4.7K Gain: 8-29.3
Gyrator - Notch/Peak Filter (Simulated inductor)
